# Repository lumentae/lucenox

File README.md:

# Lucenox

**Lucenox** — *Light in the Darkness*

---

## Overview

Lucenox is a custom mechanical keyboard with hotswappable switches which was inspired by the QWERTZ layout. It also features per key RGB with QMK!

---

## Reason

I made the project just for fun and to see if I could build my own keyboard, because I wanted something that felt exactly like my current keyboard, but in a smaller size.
Also I currently use a membrane keyboard and I thought that highway could give me an opportunity to learn how mechanical keyboards work and switch to a mechanical one.

---

## Technical Details

- **Microcontroller:** Raspberry Pi Pico 
- **Firmware:** QMK
- **Connectivity:** USB wired connection
- **LEDs:** SK6812 RGB underglow LEDs with individual addressability

---

## Assembly

## Front

## Back

## Schematic

## Case

## BOM
Quantity  | Name                   | Link                                                                                                     | Price + Shipping
--------- | ---------------------- | -------------------------------------------------------------------------------------------------------- | ----------------
3*30 (90) | Cherry MX Switch       | https://aliexpress.com/item/1005006578935785.html                                                        | 25.17€
84 (90)   | Kailh Hotswap Sockets  | https://candykeys.com/product/kailh-hot-swap-pcb-socket-black                                            | 16.00€
84 (85)   | SK6812MINI LED         | https://lcsc.com/product-detail/RGB-LEDs-Built-in-IC_OPSCO-Optoelectronics-SK6812MINI-E_C5149201.html    | 4.38€
84 (100)  | 1N4148 Diode (D)       | https://lcsc.com/product-detail/C84410.html                                                              | 1.28€
1         | LCSC Fees              | -                                                                                                        | 9.58€
1         | Raspberry Pi Pico      | https://aliexpress.com/item/1005007384675543.html                                                        | 2.79€
1         | Keycaps                | https://aliexpress.com/item/1005009489702226.html                                                        | 7.29€
1         | PCB                    | -                                                                                                        | 69.83€
1         | Total                  |                                                                                                          | 136.32€

### Total
EUR     | USD    
------- | -------
136.32€ | 158.82$

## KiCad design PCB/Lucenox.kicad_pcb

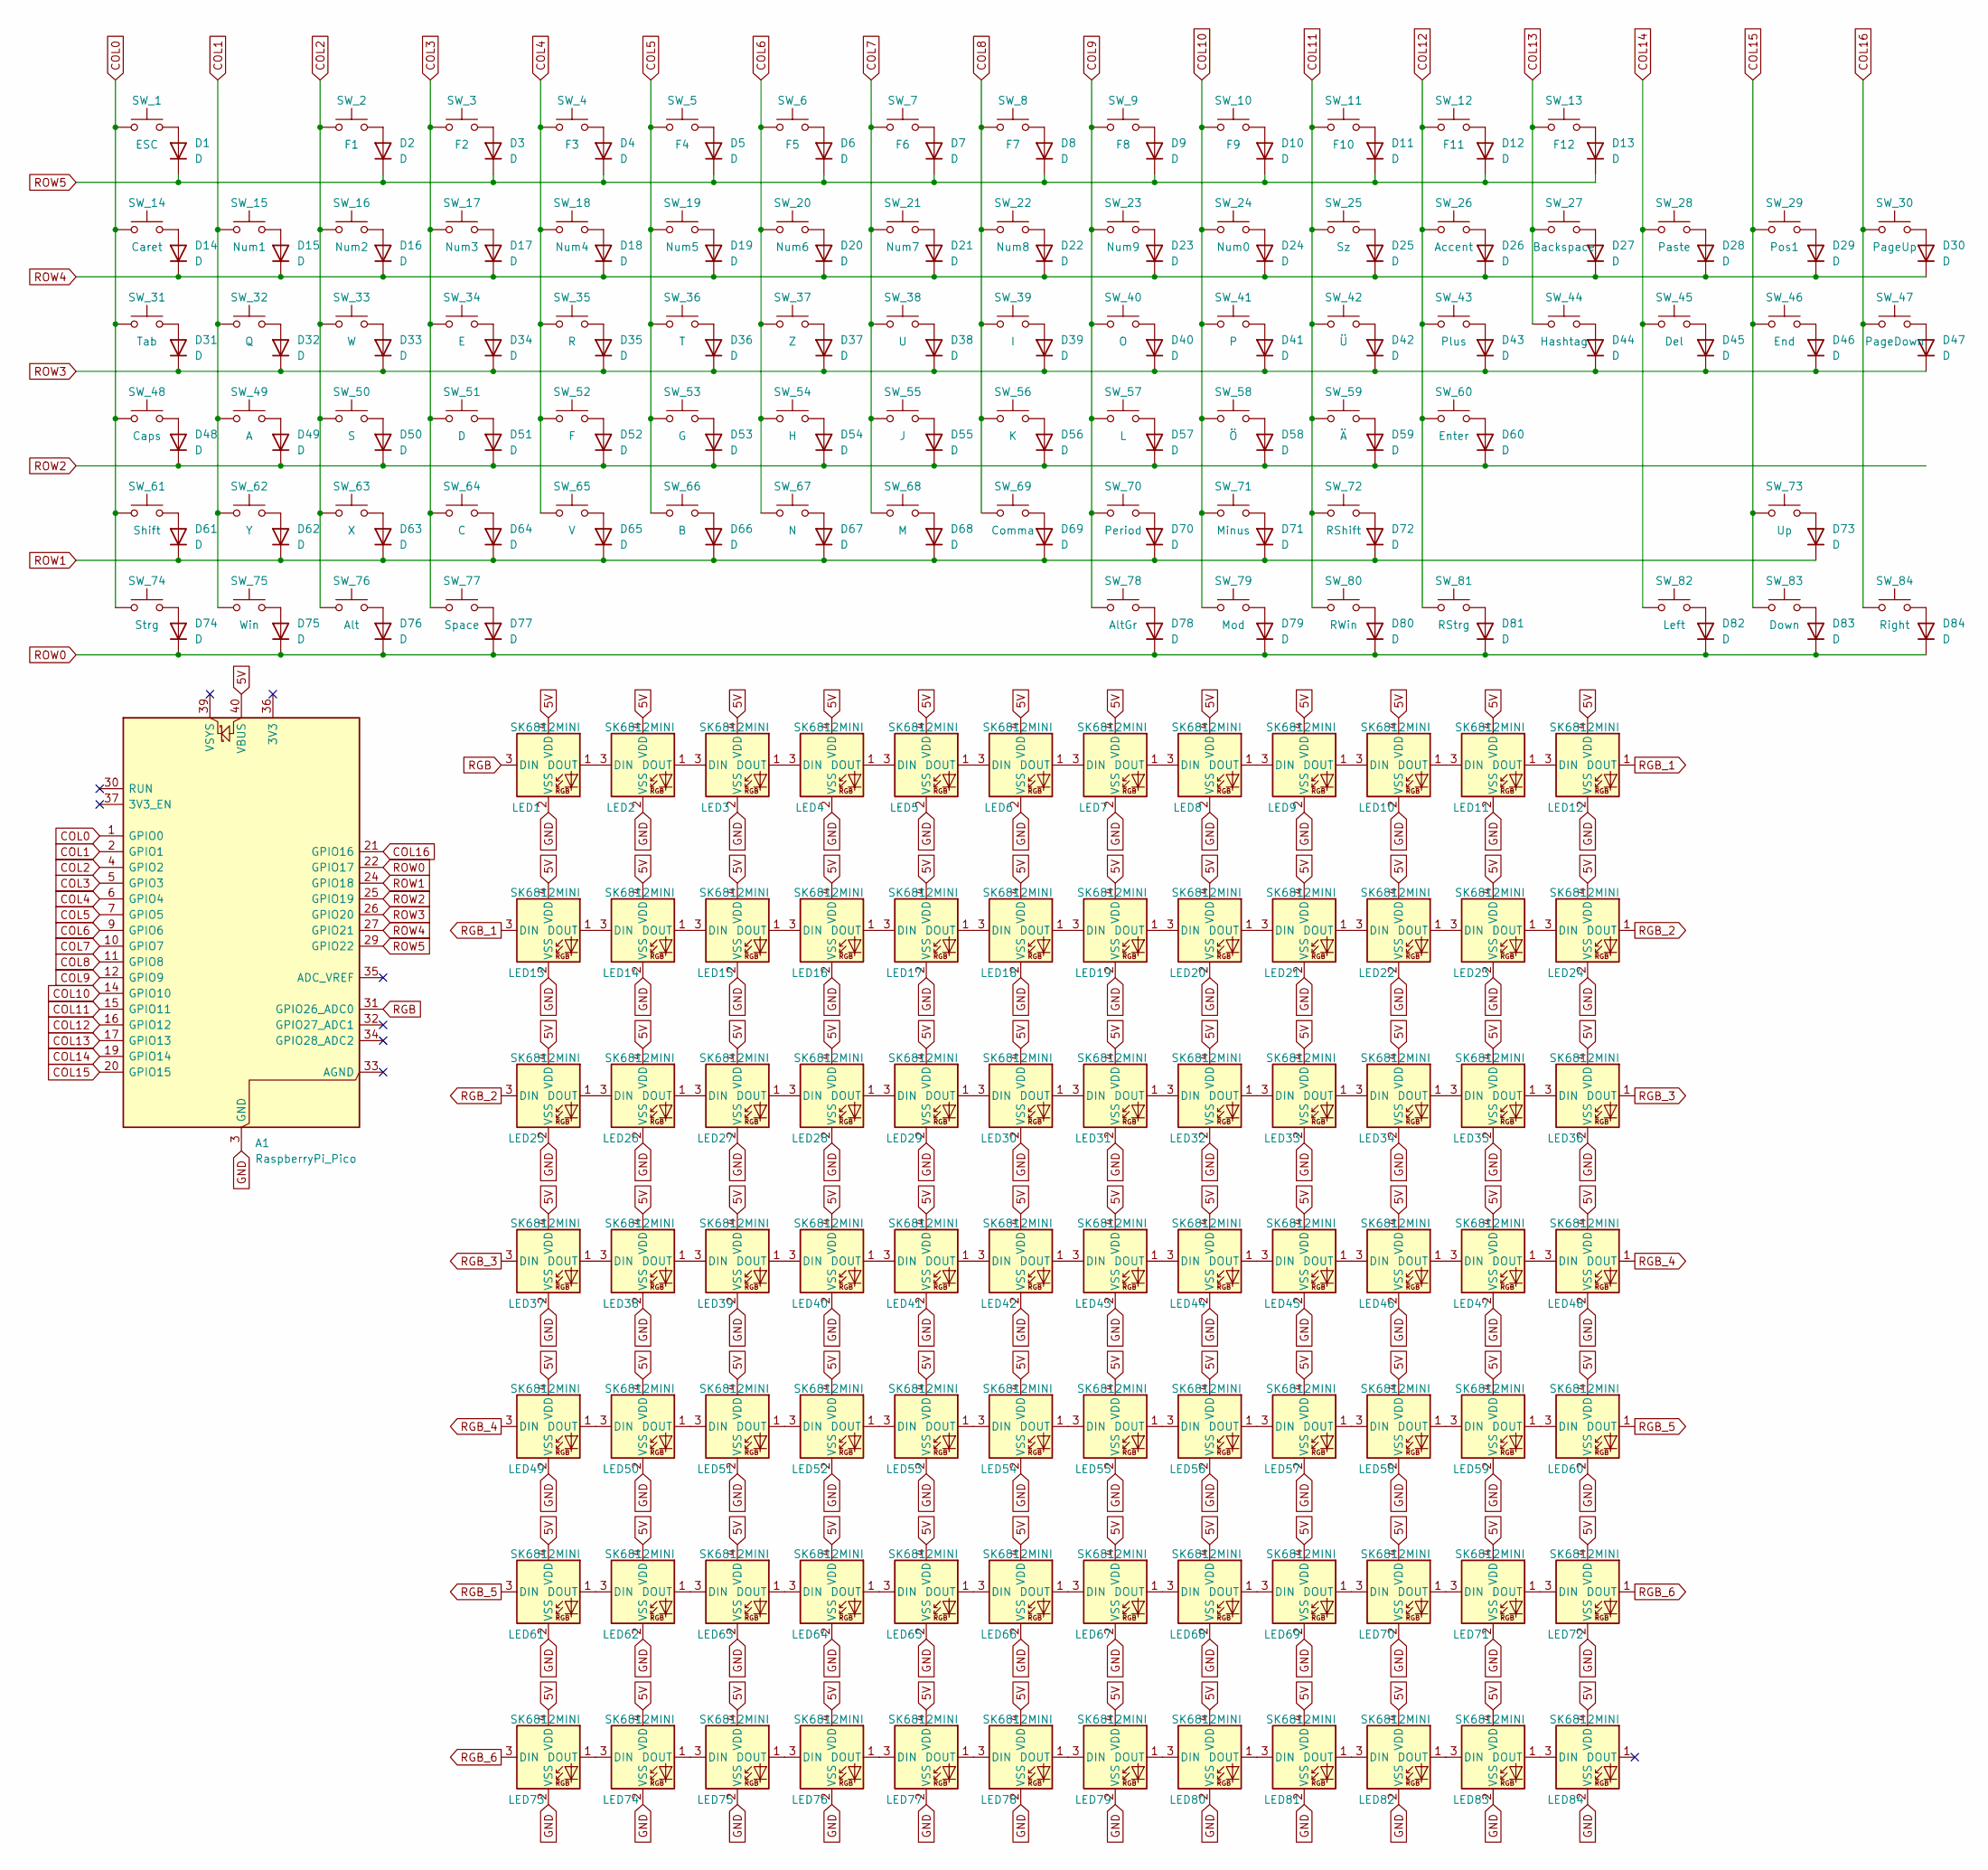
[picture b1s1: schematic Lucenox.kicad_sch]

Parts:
A1: RaspberryPi_Pico; RaspberryPi_Pico_Common_THT
D1, D2, D3, D4, D5, D6, D7, D8, D9, D10, D11, D12, D13, D14, D15, D16, D17, D18, D19, D20, D21, D22, D23, D24, D25, D26, D27, D28, D29, D30, D31, D32, D33, D34, D35, D36, D37, D38, D39, D40, D41, D42, D43, D44, D45, D46, D47, D48, D49, D50, D51, D52, D53, D54, D55, D56, D57, D58, D59, D60, D61, D62, D63, D64, D65, D66, D67, D68, D69, D70, D71, D72, D73, D74, D75, D76, D77, D78, D79, D80, D81, D82, D83, D84: D; D_DO-35_SOD27_P7.62mm_Horizontal
LED1, LED2, LED3, LED4, LED5, LED6, LED7, LED8, LED9, LED10, LED11, LED12, LED13, LED14, LED15, LED16, LED17, LED18, LED19, LED20, LED21, LED22, LED23, LED24, LED25, LED26, LED27, LED28, LED29, LED30, LED31, LED32, LED33, LED34, LED35, LED36, LED37, LED38, LED39, LED40, LED41, LED42, LED43, LED44, LED45, LED46, LED47, LED48, LED49, LED50, LED51, LED52, LED53, LED54, LED55, LED56, LED57, LED58, LED59, LED60, LED61, LED62, LED63, LED64, LED65, LED66, LED67, LED68, LED69, LED70, LED71, LED72, LED73, LED74, LED75, LED76, LED77, LED78, LED79, LED80, LED81, LED82, LED83, LED84: SK6812MINI; LED_SK6812MINI_PLCC4_3.5x3.5mm_P1.75mm
SW_1: ESC; SW_Hotswap_Kailh_MX_1.00u
SW_2: F1; SW_Hotswap_Kailh_MX_1.00u
SW_3: F2; SW_Hotswap_Kailh_MX_1.00u
SW_4: F3; SW_Hotswap_Kailh_MX_1.00u
SW_5: F4; SW_Hotswap_Kailh_MX_1.00u
SW_6: F5; SW_Hotswap_Kailh_MX_1.00u
SW_7: F6; SW_Hotswap_Kailh_MX_1.00u
SW_8: F7; SW_Hotswap_Kailh_MX_1.00u
SW_9: F8; SW_Hotswap_Kailh_MX_1.00u
SW_10: F9; SW_Hotswap_Kailh_MX_1.00u
SW_11: F10; SW_Hotswap_Kailh_MX_1.00u
SW_12: F11; SW_Hotswap_Kailh_MX_1.00u
SW_13: F12; SW_Hotswap_Kailh_MX_1.00u
SW_14: Caret; SW_Hotswap_Kailh_MX_1.00u
SW_15: Num1; SW_Hotswap_Kailh_MX_1.00u
SW_16: Num2; SW_Hotswap_Kailh_MX_1.00u
SW_17: Num3; SW_Hotswap_Kailh_MX_1.00u
SW_18: Num4; SW_Hotswap_Kailh_MX_1.00u
SW_19: Num5; SW_Hotswap_Kailh_MX_1.00u
SW_20: Num6; SW_Hotswap_Kailh_MX_1.00u
SW_21: Num7; SW_Hotswap_Kailh_MX_1.00u
SW_22: Num8; SW_Hotswap_Kailh_MX_1.00u
SW_23: Num9; SW_Hotswap_Kailh_MX_1.00u
SW_24: Num0; SW_Hotswap_Kailh_MX_1.00u
SW_25: Sz; SW_Hotswap_Kailh_MX_1.00u
SW_26: Accent; SW_Hotswap_Kailh_MX_1.00u
SW_27: Backspace; SW_Hotswap_Kailh_MX_2.00u
SW_28: Paste; SW_Hotswap_Kailh_MX_1.00u
SW_29: Pos1; SW_Hotswap_Kailh_MX_1.00u
SW_30: PageUp; SW_Hotswap_Kailh_MX_1.00u
SW_31: Tab; SW_Hotswap_Kailh_MX_1.50u
SW_32: Q; SW_Hotswap_Kailh_MX_1.00u
SW_33: W; SW_Hotswap_Kailh_MX_1.00u
SW_34: E; SW_Hotswap_Kailh_MX_1.00u
SW_35: R; SW_Hotswap_Kailh_MX_1.00u
SW_36: T; SW_Hotswap_Kailh_MX_1.00u
SW_37: Z; SW_Hotswap_Kailh_MX_1.00u
SW_38: U; SW_Hotswap_Kailh_MX_1.00u
SW_39: I; SW_Hotswap_Kailh_MX_1.00u
SW_40: O; SW_Hotswap_Kailh_MX_1.00u
SW_41: P; SW_Hotswap_Kailh_MX_1.00u
SW_42: Ü; SW_Hotswap_Kailh_MX_1.00u
SW_43: Plus; SW_Hotswap_Kailh_MX_1.00u
SW_44: Hashtag; SW_Hotswap_Kailh_MX_1.50u
SW_45: Del; SW_Hotswap_Kailh_MX_1.00u
SW_46: End; SW_Hotswap_Kailh_MX_1.00u
SW_47: PageDown; SW_Hotswap_Kailh_MX_1.00u
SW_48: Caps; SW_Hotswap_Kailh_MX_1.75u
SW_49: A; SW_Hotswap_Kailh_MX_1.00u
SW_50: S; SW_Hotswap_Kailh_MX_1.00u
SW_51: D; SW_Hotswap_Kailh_MX_1.00u
SW_52: F; SW_Hotswap_Kailh_MX_1.00u
SW_53: G; SW_Hotswap_Kailh_MX_1.00u
SW_54: H; SW_Hotswap_Kailh_MX_1.00u
SW_55: J; SW_Hotswap_Kailh_MX_1.00u
SW_56: K; SW_Hotswap_Kailh_MX_1.00u
SW_57: L; SW_Hotswap_Kailh_MX_1.00u
SW_58: Ö; SW_Hotswap_Kailh_MX_1.00u
SW_59: Ä; SW_Hotswap_Kailh_MX_1.00u
SW_60: Enter; SW_Hotswap_Kailh_MX_2.25u
SW_61: Shift; SW_Hotswap_Kailh_MX_2.25u
SW_62: Y; SW_Hotswap_Kailh_MX_1.00u
SW_63: X; SW_Hotswap_Kailh_MX_1.00u
SW_64: C; SW_Hotswap_Kailh_MX_1.00u
SW_65: V; SW_Hotswap_Kailh_MX_1.00u
SW_66: B; SW_Hotswap_Kailh_MX_1.00u
SW_67: N; SW_Hotswap_Kailh_MX_1.00u
SW_68: M; SW_Hotswap_Kailh_MX_1.00u
SW_69: Comma; SW_Hotswap_Kailh_MX_1.00u
SW_70: Period; SW_Hotswap_Kailh_MX_1.00u
SW_71: Minus; SW_Hotswap_Kailh_MX_1.00u
SW_72: RShift; SW_Hotswap_Kailh_MX_2.75u
SW_73: Up; SW_Hotswap_Kailh_MX_1.00u
SW_74: Strg; SW_Hotswap_Kailh_MX_1.25u
SW_75: Win; SW_Hotswap_Kailh_MX_1.25u
SW_76: Alt; SW_Hotswap_Kailh_MX_1.25u
SW_77: Space; SW_Hotswap_Kailh_MX_6.25u
SW_78: AltGr; SW_Hotswap_Kailh_MX_1.25u
SW_79: Mod; SW_Hotswap_Kailh_MX_1.25u
SW_80: RWin; SW_Hotswap_Kailh_MX_1.25u
SW_81: RStrg; SW_Hotswap_Kailh_MX_1.25u
SW_82: Left; SW_Hotswap_Kailh_MX_1.00u
SW_83: Down; SW_Hotswap_Kailh_MX_1.00u
SW_84: Right; SW_Hotswap_Kailh_MX_1.00u

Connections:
5V: A1.40 (VBUS), LED1.4 (VDD), LED2.4 (VDD), LED3.4 (VDD), LED4.4 (VDD), LED5.4 (VDD), LED6.4 (VDD), LED7.4 (VDD), LED8.4 (VDD), LED9.4 (VDD), LED10.4 (VDD), LED11.4 (VDD), LED12.4 (VDD), LED13.4 (VDD), LED14.4 (VDD), LED15.4 (VDD), LED16.4 (VDD), LED17.4 (VDD), LED18.4 (VDD), LED19.4 (VDD), LED20.4 (VDD), LED21.4 (VDD), LED22.4 (VDD), LED23.4 (VDD), LED24.4 (VDD), LED25.4 (VDD), LED26.4 (VDD), LED27.4 (VDD), LED28.4 (VDD), LED29.4 (VDD), LED30.4 (VDD), LED31.4 (VDD), LED32.4 (VDD), LED33.4 (VDD), LED34.4 (VDD), LED35.4 (VDD), LED36.4 (VDD), LED37.4 (VDD), LED38.4 (VDD), LED39.4 (VDD), LED40.4 (VDD), LED41.4 (VDD), LED42.4 (VDD), LED43.4 (VDD), LED44.4 (VDD), LED45.4 (VDD), LED46.4 (VDD), LED47.4 (VDD), LED48.4 (VDD), LED49.4 (VDD), LED50.4 (VDD), LED51.4 (VDD), LED52.4 (VDD), LED53.4 (VDD), LED54.4 (VDD), LED55.4 (VDD), LED56.4 (VDD), LED57.4 (VDD), LED58.4 (VDD), LED59.4 (VDD), LED60.4 (VDD), LED61.4 (VDD), LED62.4 (VDD), LED63.4 (VDD), LED64.4 (VDD), LED65.4 (VDD), LED66.4 (VDD), LED67.4 (VDD), LED68.4 (VDD), LED69.4 (VDD), LED70.4 (VDD), LED71.4 (VDD), LED72.4 (VDD), LED73.4 (VDD), LED74.4 (VDD), LED75.4 (VDD), LED76.4 (VDD), LED77.4 (VDD), LED78.4 (VDD), LED79.4 (VDD), LED80.4 (VDD), LED81.4 (VDD), LED82.4 (VDD), LED83.4 (VDD), LED84.4 (VDD)
COL0: A1.1 (GPIO0), SW_1.1, SW_14.1, SW_31.1, SW_48.1, SW_61.1, SW_74.1
COL1: A1.2 (GPIO1), SW_15.1, SW_32.1, SW_49.1, SW_62.1, SW_75.1
COL2: A1.4 (GPIO2), SW_2.1, SW_16.1, SW_33.1, SW_50.1, SW_63.1, SW_76.1
COL3: A1.5 (GPIO3), SW_3.1, SW_17.1, SW_34.1, SW_51.1, SW_64.1, SW_77.1
COL4: A1.6 (GPIO4), SW_4.1, SW_18.1, SW_35.1, SW_52.1, SW_65.1
COL5: A1.7 (GPIO5), SW_5.1, SW_19.1, SW_36.1, SW_53.1, SW_66.1
COL6: A1.9 (GPIO6), SW_6.1, SW_20.1, SW_37.1, SW_54.1, SW_67.1
COL7: A1.10 (GPIO7), SW_7.1, SW_21.1, SW_38.1, SW_55.1, SW_68.1
COL8: A1.11 (GPIO8), SW_8.1, SW_22.1, SW_39.1, SW_56.1, SW_69.1
COL9: A1.12 (GPIO9), SW_9.1, SW_23.1, SW_40.1, SW_57.1, SW_70.1, SW_78.1
COL10: A1.14 (GPIO10), SW_10.1, SW_24.1, SW_41.1, SW_58.1, SW_71.1, SW_79.1
COL11: A1.15 (GPIO11), SW_11.1, SW_25.1, SW_42.1, SW_59.1, SW_72.1, SW_80.1
COL12: A1.16 (GPIO12), SW_12.1, SW_26.1, SW_43.1, SW_60.1, SW_81.1
COL13: A1.17 (GPIO13), SW_13.1, SW_27.1, SW_44.1
COL14: A1.19 (GPIO14), SW_28.1, SW_45.1, SW_82.1
COL15: A1.20 (GPIO15), SW_29.1, SW_46.1, SW_73.1, SW_83.1
COL16: A1.21 (GPIO16), SW_30.1, SW_47.1, SW_84.1
GND: A1.3 (GND), A1.8 (GND), A1.13 (GND), A1.18 (GND), A1.23 (GND), A1.28 (GND), A1.38 (GND), LED1.2 (VSS), LED2.2 (VSS), LED3.2 (VSS), LED4.2 (VSS), LED5.2 (VSS), LED6.2 (VSS), LED7.2 (VSS), LED8.2 (VSS), LED9.2 (VSS), LED10.2 (VSS), LED11.2 (VSS), LED12.2 (VSS), LED13.2 (VSS), LED14.2 (VSS), LED15.2 (VSS), LED16.2 (VSS), LED17.2 (VSS), LED18.2 (VSS), LED19.2 (VSS), LED20.2 (VSS), LED21.2 (VSS), LED22.2 (VSS), LED23.2 (VSS), LED24.2 (VSS), LED25.2 (VSS), LED26.2 (VSS), LED27.2 (VSS), LED28.2 (VSS), LED29.2 (VSS), LED30.2 (VSS), LED31.2 (VSS), LED32.2 (VSS), LED33.2 (VSS), LED34.2 (VSS), LED35.2 (VSS), LED36.2 (VSS), LED37.2 (VSS), LED38.2 (VSS), LED39.2 (VSS), LED40.2 (VSS), LED41.2 (VSS), LED42.2 (VSS), LED43.2 (VSS), LED44.2 (VSS), LED45.2 (VSS), LED46.2 (VSS), LED47.2 (VSS), LED48.2 (VSS), LED49.2 (VSS), LED50.2 (VSS), LED51.2 (VSS), LED52.2 (VSS), LED53.2 (VSS), LED54.2 (VSS), LED55.2 (VSS), LED56.2 (VSS), LED57.2 (VSS), LED58.2 (VSS), LED59.2 (VSS), LED60.2 (VSS), LED61.2 (VSS), LED62.2 (VSS), LED63.2 (VSS), LED64.2 (VSS), LED65.2 (VSS), LED66.2 (VSS), LED67.2 (VSS), LED68.2 (VSS), LED69.2 (VSS), LED70.2 (VSS), LED71.2 (VSS), LED72.2 (VSS), LED73.2 (VSS), LED74.2 (VSS), LED75.2 (VSS), LED76.2 (VSS), LED77.2 (VSS), LED78.2 (VSS), LED79.2 (VSS), LED80.2 (VSS), LED81.2 (VSS), LED82.2 (VSS), LED83.2 (VSS), LED84.2 (VSS)
unnamed: D1.2 (A), SW_1.2
unnamed: D2.2 (A), SW_2.2
unnamed: D3.2 (A), SW_3.2
unnamed: D4.2 (A), SW_4.2
unnamed: D5.2 (A), SW_5.2
unnamed: D6.2 (A), SW_6.2
unnamed: D7.2 (A), SW_7.2
unnamed: D8.2 (A), SW_8.2
unnamed: D9.2 (A), SW_9.2
unnamed: D10.2 (A), SW_10.2
unnamed: D11.2 (A), SW_11.2
unnamed: D12.2 (A), SW_12.2
unnamed: D13.2 (A), SW_13.2
unnamed: D14.2 (A), SW_14.2
unnamed: D15.2 (A), SW_15.2
unnamed: D16.2 (A), SW_16.2
unnamed: D17.2 (A), SW_17.2
unnamed: D18.2 (A), SW_18.2
unnamed: D19.2 (A), SW_19.2
unnamed: D20.2 (A), SW_20.2
unnamed: D21.2 (A), SW_21.2
unnamed: D22.2 (A), SW_22.2
unnamed: D23.2 (A), SW_23.2
unnamed: D24.2 (A), SW_24.2
unnamed: D25.2 (A), SW_25.2
unnamed: D26.2 (A), SW_26.2
unnamed: D27.2 (A), SW_27.2
unnamed: D28.2 (A), SW_28.2
unnamed: D29.2 (A), SW_29.2
unnamed: D30.2 (A), SW_30.2
unnamed: D31.2 (A), SW_31.2
unnamed: D32.2 (A), SW_32.2
unnamed: D33.2 (A), SW_33.2
unnamed: D34.2 (A), SW_34.2
unnamed: D35.2 (A), SW_35.2
unnamed: D36.2 (A), SW_36.2
unnamed: D37.2 (A), SW_37.2
unnamed: D38.2 (A), SW_38.2
unnamed: D39.2 (A), SW_39.2
unnamed: D40.2 (A), SW_40.2
unnamed: D41.2 (A), SW_41.2
unnamed: D42.2 (A), SW_42.2
unnamed: D43.2 (A), SW_43.2
unnamed: D44.2 (A), SW_44.2
unnamed: D45.2 (A), SW_45.2
unnamed: D46.2 (A), SW_46.2
unnamed: D47.2 (A), SW_47.2
unnamed: D48.2 (A), SW_48.2
unnamed: D49.2 (A), SW_49.2
unnamed: D50.2 (A), SW_50.2
unnamed: D51.2 (A), SW_51.2
unnamed: D52.2 (A), SW_52.2
unnamed: D53.2 (A), SW_53.2
unnamed: D54.2 (A), SW_54.2
unnamed: D55.2 (A), SW_55.2
unnamed: D56.2 (A), SW_56.2
unnamed: D57.2 (A), SW_57.2
unnamed: D58.2 (A), SW_58.2
unnamed: D59.2 (A), SW_59.2
unnamed: D60.2 (A), SW_60.2
unnamed: D61.2 (A), SW_61.2
unnamed: D62.2 (A), SW_62.2
unnamed: D63.2 (A), SW_63.2
unnamed: D64.2 (A), SW_64.2
unnamed: D65.2 (A), SW_65.2
unnamed: D66.2 (A), SW_66.2
unnamed: D67.2 (A), SW_67.2
unnamed: D68.2 (A), SW_68.2
unnamed: D69.2 (A), SW_69.2
unnamed: D70.2 (A), SW_70.2
unnamed: D71.2 (A), SW_71.2
unnamed: D72.2 (A), SW_72.2
unnamed: D73.2 (A), SW_73.2
unnamed: D74.2 (A), SW_74.2
unnamed: D75.2 (A), SW_75.2
unnamed: D76.2 (A), SW_76.2
unnamed: D77.2 (A), SW_77.2
unnamed: D78.2 (A), SW_78.2
unnamed: D79.2 (A), SW_79.2
unnamed: D80.2 (A), SW_80.2
unnamed: D81.2 (A), SW_81.2
unnamed: D82.2 (A), SW_82.2
unnamed: D83.2 (A), SW_83.2
unnamed: D84.2 (A), SW_84.2
unnamed: LED1.1 (DOUT), LED2.3 (DIN)
unnamed: LED2.1 (DOUT), LED3.3 (DIN)
unnamed: LED3.1 (DOUT), LED4.3 (DIN)
unnamed: LED4.1 (DOUT), LED5.3 (DIN)
unnamed: LED5.1 (DOUT), LED6.3 (DIN)
unnamed: LED6.1 (DOUT), LED7.3 (DIN)
unnamed: LED7.1 (DOUT), LED8.3 (DIN)
unnamed: LED8.1 (DOUT), LED9.3 (DIN)
unnamed: LED9.1 (DOUT), LED10.3 (DIN)
unnamed: LED10.1 (DOUT), LED11.3 (DIN)
unnamed: LED11.1 (DOUT), LED12.3 (DIN)
unnamed: LED13.1 (DOUT), LED14.3 (DIN)
unnamed: LED14.1 (DOUT), LED15.3 (DIN)
unnamed: LED15.1 (DOUT), LED16.3 (DIN)
unnamed: LED16.1 (DOUT), LED17.3 (DIN)
unnamed: LED17.1 (DOUT), LED18.3 (DIN)
unnamed: LED18.1 (DOUT), LED19.3 (DIN)
unnamed: LED19.1 (DOUT), LED20.3 (DIN)
unnamed: LED20.1 (DOUT), LED21.3 (DIN)
unnamed: LED21.1 (DOUT), LED22.3 (DIN)
unnamed: LED22.1 (DOUT), LED23.3 (DIN)
unnamed: LED23.1 (DOUT), LED24.3 (DIN)
unnamed: LED25.1 (DOUT), LED26.3 (DIN)
unnamed: LED26.1 (DOUT), LED27.3 (DIN)
unnamed: LED27.1 (DOUT), LED28.3 (DIN)
unnamed: LED28.1 (DOUT), LED29.3 (DIN)
unnamed: LED29.1 (DOUT), LED30.3 (DIN)
unnamed: LED30.1 (DOUT), LED31.3 (DIN)
unnamed: LED31.1 (DOUT), LED32.3 (DIN)
unnamed: LED32.1 (DOUT), LED33.3 (DIN)
unnamed: LED33.1 (DOUT), LED34.3 (DIN)
unnamed: LED34.1 (DOUT), LED35.3 (DIN)
unnamed: LED35.1 (DOUT), LED36.3 (DIN)
unnamed: LED37.1 (DOUT), LED38.3 (DIN)
unnamed: LED38.1 (DOUT), LED39.3 (DIN)
unnamed: LED39.1 (DOUT), LED40.3 (DIN)
unnamed: LED40.1 (DOUT), LED41.3 (DIN)
unnamed: LED41.1 (DOUT), LED42.3 (DIN)
unnamed: LED42.1 (DOUT), LED43.3 (DIN)
unnamed: LED43.1 (DOUT), LED44.3 (DIN)
unnamed: LED44.1 (DOUT), LED45.3 (DIN)
unnamed: LED45.1 (DOUT), LED46.3 (DIN)
unnamed: LED46.1 (DOUT), LED47.3 (DIN)
unnamed: LED47.1 (DOUT), LED48.3 (DIN)
unnamed: LED49.1 (DOUT), LED50.3 (DIN)
unnamed: LED50.1 (DOUT), LED51.3 (DIN)
unnamed: LED51.1 (DOUT), LED52.3 (DIN)
unnamed: LED52.1 (DOUT), LED53.3 (DIN)
unnamed: LED53.1 (DOUT), LED54.3 (DIN)
unnamed: LED54.1 (DOUT), LED55.3 (DIN)
unnamed: LED55.1 (DOUT), LED56.3 (DIN)
unnamed: LED56.1 (DOUT), LED57.3 (DIN)
unnamed: LED57.1 (DOUT), LED58.3 (DIN)
unnamed: LED58.1 (DOUT), LED59.3 (DIN)
unnamed: LED59.1 (DOUT), LED60.3 (DIN)
unnamed: LED61.1 (DOUT), LED62.3 (DIN)
unnamed: LED62.1 (DOUT), LED63.3 (DIN)
unnamed: LED63.1 (DOUT), LED64.3 (DIN)
unnamed: LED64.1 (DOUT), LED65.3 (DIN)
unnamed: LED65.1 (DOUT), LED66.3 (DIN)
unnamed: LED66.1 (DOUT), LED67.3 (DIN)
unnamed: LED67.1 (DOUT), LED68.3 (DIN)
unnamed: LED68.1 (DOUT), LED69.3 (DIN)
unnamed: LED69.1 (DOUT), LED70.3 (DIN)
unnamed: LED70.1 (DOUT), LED71.3 (DIN)
unnamed: LED71.1 (DOUT), LED72.3 (DIN)
unnamed: LED73.1 (DOUT), LED74.3 (DIN)
unnamed: LED74.1 (DOUT), LED75.3 (DIN)
unnamed: LED75.1 (DOUT), LED76.3 (DIN)
unnamed: LED76.1 (DOUT), LED77.3 (DIN)
unnamed: LED77.1 (DOUT), LED78.3 (DIN)
unnamed: LED78.1 (DOUT), LED79.3 (DIN)
unnamed: LED79.1 (DOUT), LED80.3 (DIN)
unnamed: LED80.1 (DOUT), LED81.3 (DIN)
unnamed: LED81.1 (DOUT), LED82.3 (DIN)
unnamed: LED82.1 (DOUT), LED83.3 (DIN)
unnamed: LED83.1 (DOUT), LED84.3 (DIN)
RGB: A1.31 (GPIO26_ADC0), LED1.3 (DIN)
RGB_1: LED12.1 (DOUT), LED13.3 (DIN)
RGB_2: LED24.1 (DOUT), LED25.3 (DIN)
RGB_3: LED36.1 (DOUT), LED37.3 (DIN)
RGB_4: LED48.1 (DOUT), LED49.3 (DIN)
RGB_5: LED60.1 (DOUT), LED61.3 (DIN)
RGB_6: LED72.1 (DOUT), LED73.3 (DIN)
ROW0: A1.22 (GPIO17), D74.1 (K), D75.1 (K), D76.1 (K), D77.1 (K), D78.1 (K), D79.1 (K), D80.1 (K), D81.1 (K), D82.1 (K), D83.1 (K), D84.1 (K)
ROW1: A1.24 (GPIO18), D61.1 (K), D62.1 (K), D63.1 (K), D64.1 (K), D65.1 (K), D66.1 (K), D67.1 (K), D68.1 (K), D69.1 (K), D70.1 (K), D71.1 (K), D72.1 (K), D73.1 (K)
ROW2: A1.25 (GPIO19), D48.1 (K), D49.1 (K), D50.1 (K), D51.1 (K), D52.1 (K), D53.1 (K), D54.1 (K), D55.1 (K), D56.1 (K), D57.1 (K), D58.1 (K), D59.1 (K), D60.1 (K)
ROW3: A1.26 (GPIO20), D31.1 (K), D32.1 (K), D33.1 (K), D34.1 (K), D35.1 (K), D36.1 (K), D37.1 (K), D38.1 (K), D39.1 (K), D40.1 (K), D41.1 (K), D42.1 (K), D43.1 (K), D44.1 (K), D45.1 (K), D46.1 (K), D47.1 (K)
ROW4: A1.27 (GPIO21), D14.1 (K), D15.1 (K), D16.1 (K), D17.1 (K), D18.1 (K), D19.1 (K), D20.1 (K), D21.1 (K), D22.1 (K), D23.1 (K), D24.1 (K), D25.1 (K), D26.1 (K), D27.1 (K), D28.1 (K), D29.1 (K), D30.1 (K)
ROW5: A1.29 (GPIO22), D1.1 (K), D2.1 (K), D3.1 (K), D4.1 (K), D5.1 (K), D6.1 (K), D7.1 (K), D8.1 (K), D9.1 (K), D10.1 (K), D11.1 (K), D12.1 (K), D13.1 (K)

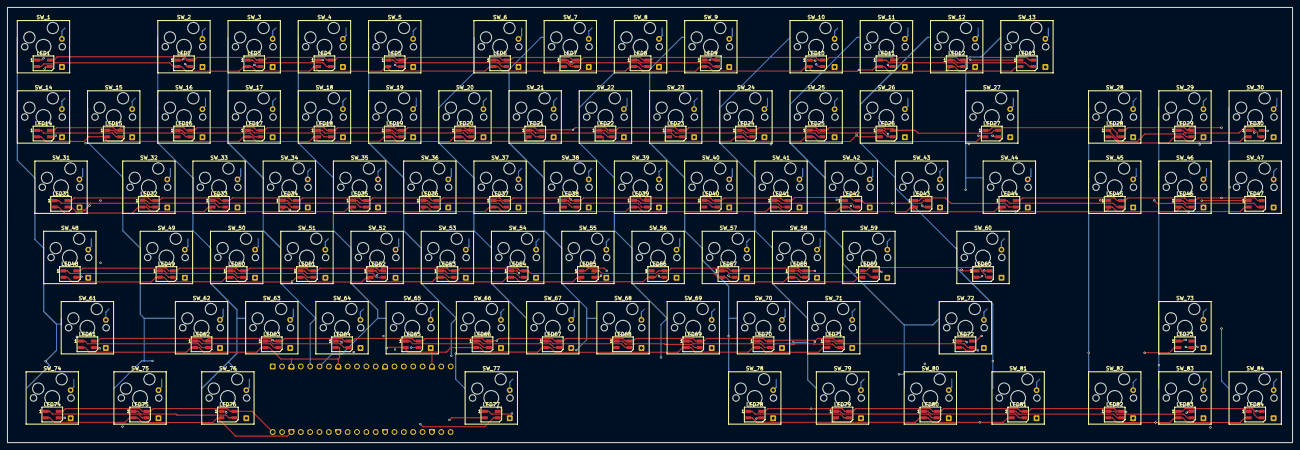
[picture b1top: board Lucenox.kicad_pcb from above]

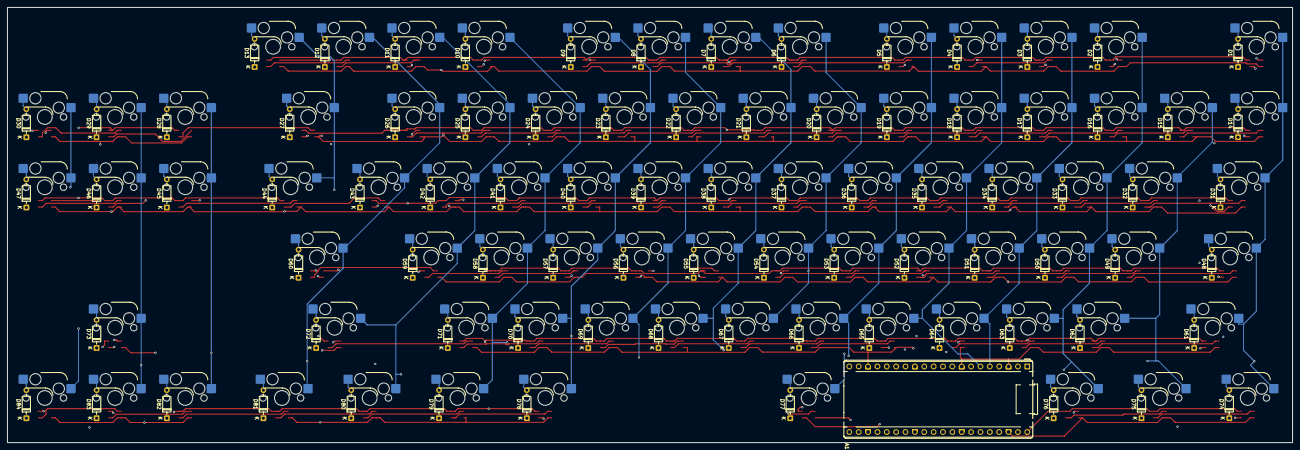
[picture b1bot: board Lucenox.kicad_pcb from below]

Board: 4 copper layers, 348.5 x 118.0 mm, 253 parts (85 on the bottom side), 193 nets.

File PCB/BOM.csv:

"Id";"Designator";"Footprint";"Quantity";"Designation";"Supplier and ref";
1;"SW_76";"SW_Hotswap_Kailh_MX_1.25u";1;"Alt";;;
2;"SW_48";"SW_Hotswap_Kailh_MX_1.75u";1;"Caps";;;
3;"LED71,LED56,LED1,LED78,LED81,LED41,LED16,LED65,LED30,LED24,LED33,LED35,LED73,LED4,LED15,LED62,LED42,LED46,LED14,LED2,LED32,LED23,LED47,LED13,LED66,LED50,LED82,LED20,LED49,LED60,LED7,LED5,LED11,LED63,LED79,LED74,LED21,LED69,LED59,LED57,LED10,LED37,LED3,LED84,LED55,LED6,LED29,LED22,LED68,LED39,LED27,LED45,LED61,LED38,LED25,LED83,LED53,LED17,LED8,LED19,LED58,LED54,LED75,LED77,LED28,LED36,LED52,LED67,LED26,LED76,LED70,LED9,LED40,LED34,LED18,LED48,LED44,LED31,LED80,LED43,LED12,LED64,LED51,LED72";"LED_SK6812MINI_PLCC4_3.5x3.5mm_P1.75mm";84;"SK6812MINI";;;
4;"SW_12";"SW_Hotswap_Kailh_MX_1.00u";1;"F11";;;
5;"SW_71";"SW_Hotswap_Kailh_MX_1.00u";1;"Minus";;;
6;"SW_45";"SW_Hotswap_Kailh_MX_1.00u";1;"Del";;;
7;"SW_37";"SW_Hotswap_Kailh_MX_1.00u";1;"Z";;;
8;"SW_16";"SW_Hotswap_Kailh_MX_1.00u";1;"Num2";;;
9;"SW_60";"SW_Hotswap_Kailh_MX_2.25u";1;"Enter";;;
10;"SW_14";"SW_Hotswap_Kailh_MX_1.00u";1;"Caret";;;
11;"SW_72";"SW_Hotswap_Kailh_MX_2.75u";1;"RShift";;;
12;"SW_7";"SW_Hotswap_Kailh_MX_1.00u";1;"F6";;;
13;"SW_43";"SW_Hotswap_Kailh_MX_1.00u";1;"Plus";;;
14;"SW_11";"SW_Hotswap_Kailh_MX_1.00u";1;"F10";;;
15;"SW_24";"SW_Hotswap_Kailh_MX_1.00u";1;"Num0";;;
16;"SW_84";"SW_Hotswap_Kailh_MX_1.00u";1;"Right";;;
17;"SW_34";"SW_Hotswap_Kailh_MX_1.00u";1;"E";;;
18;"SW_54";"SW_Hotswap_Kailh_MX_1.00u";1;"H";;;
19;"SW_49";"SW_Hotswap_Kailh_MX_1.00u";1;"A";;;
20;"SW_19";"SW_Hotswap_Kailh_MX_1.00u";1;"Num5";;;
21;"SW_8";"SW_Hotswap_Kailh_MX_1.00u";1;"F7";;;
22;"SW_26";"SW_Hotswap_Kailh_MX_1.00u";1;"Accent";;;
23;"SW_13";"SW_Hotswap_Kailh_MX_1.00u";1;"F12";;;
24;"SW_33";"SW_Hotswap_Kailh_MX_1.00u";1;"W";;;
25;"SW_58";"SW_Hotswap_Kailh_MX_1.00u";1;"Ö";;;
26;"SW_17";"SW_Hotswap_Kailh_MX_1.00u";1;"Num3";;;
27;"SW_9";"SW_Hotswap_Kailh_MX_1.00u";1;"F8";;;
28;"SW_75";"SW_Hotswap_Kailh_MX_1.25u";1;"Win";;;
29;"SW_79";"SW_Hotswap_Kailh_MX_1.25u";1;"Mod";;;
30;"SW_62";"SW_Hotswap_Kailh_MX_1.00u";1;"Y";;;
31;"SW_82";"SW_Hotswap_Kailh_MX_1.00u";1;"Left";;;
32;"SW_66";"SW_Hotswap_Kailh_MX_1.00u";1;"B";;;
33;"SW_47";"SW_Hotswap_Kailh_MX_1.00u";1;"PageDown";;;
34;"SW_35";"SW_Hotswap_Kailh_MX_1.00u";1;"R";;;
35;"SW_55";"SW_Hotswap_Kailh_MX_1.00u";1;"J";;;
36;"SW_59";"SW_Hotswap_Kailh_MX_1.00u";1;"Ä";;;
37;"SW_56";"SW_Hotswap_Kailh_MX_1.00u";1;"K";;;
38;"SW_39";"SW_Hotswap_Kailh_MX_1.00u";1;"I";;;
39;"SW_28";"SW_Hotswap_Kailh_MX_1.00u";1;"Paste";;;
40;"SW_65";"SW_Hotswap_Kailh_MX_1.00u";1;"V";;;
41;"SW_57";"SW_Hotswap_Kailh_MX_1.00u";1;"L";;;
42;"SW_30";"SW_Hotswap_Kailh_MX_1.00u";1;"PageUp";;;
43;"SW_36";"SW_Hotswap_Kailh_MX_1.00u";1;"T";;;
44;"SW_52";"SW_Hotswap_Kailh_MX_1.00u";1;"F";;;
45;"SW_5";"SW_Hotswap_Kailh_MX_1.00u";1;"F4";;;
46;"SW_63";"SW_Hotswap_Kailh_MX_1.00u";1;"X";;;
47;"SW_41";"SW_Hotswap_Kailh_MX_1.00u";1;"P";;;
48;"SW_74";"SW_Hotswap_Kailh_MX_1.25u";1;"Strg";;;
49;"SW_51";"SW_Hotswap_Kailh_MX_1.00u";1;"D";;;
50;"SW_2";"SW_Hotswap_Kailh_MX_1.00u";1;"F1";;;
51;"SW_61";"SW_Hotswap_Kailh_MX_2.25u";1;"Shift";;;
52;"SW_78";"SW_Hotswap_Kailh_MX_1.25u";1;"AltGr";;;
53;"SW_68";"SW_Hotswap_Kailh_MX_1.00u";1;"M";;;
54;"SW_53";"SW_Hotswap_Kailh_MX_1.00u";1;"G";;;
55;"SW_69";"SW_Hotswap_Kailh_MX_1.00u";1;"Comma";;;
56;"SW_29";"SW_Hotswap_Kailh_MX_1.00u";1;"Pos1";;;
57;"SW_50";"SW_Hotswap_Kailh_MX_1.00u";1;"S";;;
58;"SW_20";"SW_Hotswap_Kailh_MX_1.00u";1;"Num6";;;
59;"SW_15";"SW_Hotswap_Kailh_MX_1.00u";1;"Num1";;;
60;"SW_32";"SW_Hotswap_Kailh_MX_1.00u";1;"Q";;;
61;"SW_1";"SW_Hotswap_Kailh_MX_1.00u";1;"ESC";;;
62;"SW_83";"SW_Hotswap_Kailh_MX_1.00u";1;"Down";;;
63;"SW_81";"SW_Hotswap_Kailh_MX_1.25u";1;"RStrg";;;
64;"SW_44";"SW_Hotswap_Kailh_MX_1.50u";1;"Hashtag";;;
65;"SW_23";"SW_Hotswap_Kailh_MX_1.00u";1;"Num9";;;
66;"SW_18";"SW_Hotswap_Kailh_MX_1.00u";1;"Num4";;;
67;"SW_40";"SW_Hotswap_Kailh_MX_1.00u";1;"O";;;
68;"SW_67";"SW_Hotswap_Kailh_MX_1.00u";1;"N";;;
69;"SW_3";"SW_Hotswap_Kailh_MX_1.00u";1;"F2";;;
70;"SW_42";"SW_Hotswap_Kailh_MX_1.00u";1;"Ü";;;
71;"SW_27";"SW_Hotswap_Kailh_MX_2.00u";1;"Backspace";;;
72;"SW_4";"SW_Hotswap_Kailh_MX_1.00u";1;"F3";;;
73;"SW_64";"SW_Hotswap_Kailh_MX_1.00u";1;"C";;;
74;"SW_80";"SW_Hotswap_Kailh_MX_1.25u";1;"RWin";;;
75;"SW_6";"SW_Hotswap_Kailh_MX_1.00u";1;"F5";;;
76;"SW_21";"SW_Hotswap_Kailh_MX_1.00u";1;"Num7";;;
77;"SW_77";"SW_Hotswap_Kailh_MX_6.25u";1;"Space";;;
78;"SW_73";"SW_Hotswap_Kailh_MX_1.00u";1;"Up";;;
79;"SW_46";"SW_Hotswap_Kailh_MX_1.00u";1;"End";;;
80;"SW_31";"SW_Hotswap_Kailh_MX_1.50u";1;"Tab";;;
81;"SW_38";"SW_Hotswap_Kailh_MX_1.00u";1;"U";;;
82;"SW_25";"SW_Hotswap_Kailh_MX_1.00u";1;"Sz";;;
83;"SW_10";"SW_Hotswap_Kailh_MX_1.00u";1;"F9";;;
84;"SW_22";"SW_Hotswap_Kailh_MX_1.00u";1;"Num8";;;
85;"SW_70";"SW_Hotswap_Kailh_MX_1.00u";1;"Period";;;
86;"D78,D36,D22,D40,D52,D26,D49,D19,D83,D5,D72,D44,D39,D6,D76,D82,D38,D74,D4,D68,D12,D48,D80,D28,D59,D81,D45,D66,D58,D2,D62,D84,D23,D10,D24,D35,D56,D31,D18,D8,D65,D64,D1,D73,D46,D30,D67,D20,D77,D63,D16,D69,D21,D3,D60,D70,D79,D61,D27,D55,D15,D75,D11,D71,D34,D47,D41,D17,D37,D43,D13,D29,D14,D42,D32,D25,D53,D7,D33,D50,D9,D51,D57,D54";"D_0805_2012Metric";84;"D";;;
87;"A1";"RaspberryPi_Pico_Common_THT";1;"RaspberryPi_Pico";;;

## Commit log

2025-06-19 Create delete
2025-06-19 Modify Journal
2025-06-19 Update JOURNAL.md to include time spent on tasks
2025-06-23 Add project files
2025-07-24 Finish BOM and CAD Model
2025-07-24 Finish BOM as csv
2025-07-24 Update BOM.csv to include Euro symbol in price column
2025-07-24 Cheaper LCSC fees but 4€ kailh socket shipping
2025-07-24 PCB costs more than expected
2025-07-25 Add firmware
2025-07-25 Update README.md to clarify keyboard features and design inspiration
2025-07-25 Refactor README.md
2025-07-25 Fix punctuation
2025-08-10 Switch to THT Diodes
2025-08-10 Add assembly
